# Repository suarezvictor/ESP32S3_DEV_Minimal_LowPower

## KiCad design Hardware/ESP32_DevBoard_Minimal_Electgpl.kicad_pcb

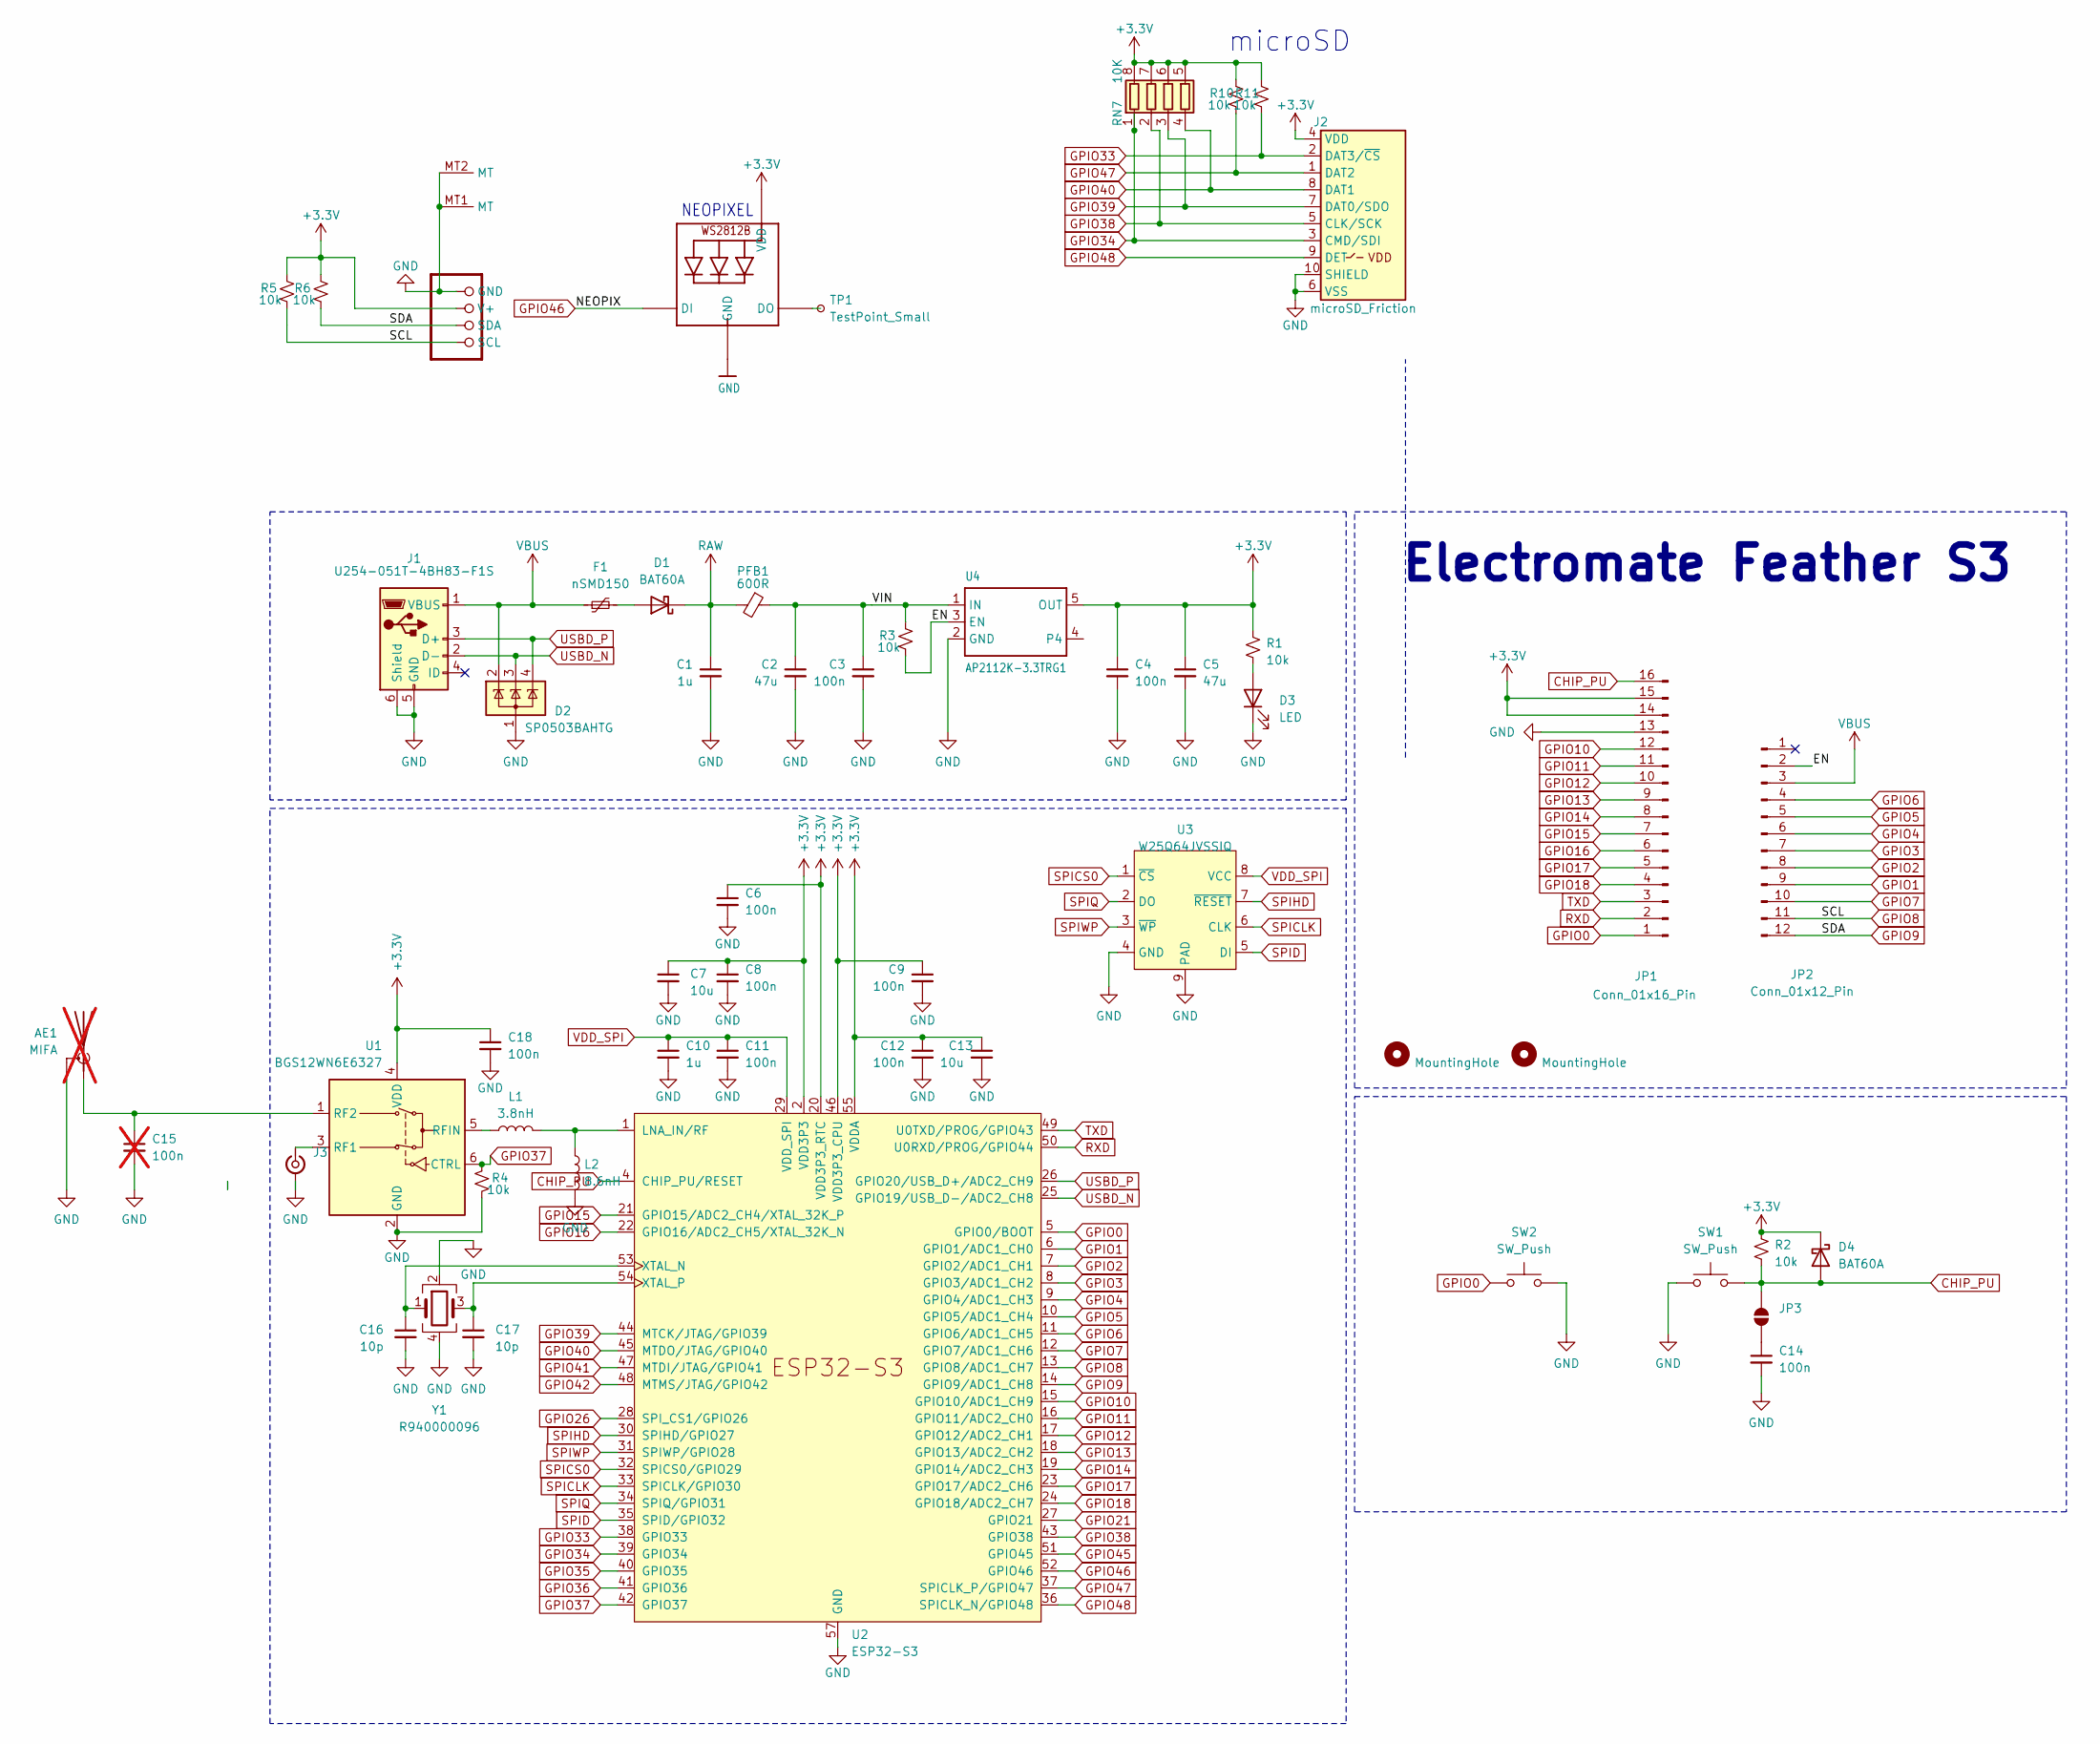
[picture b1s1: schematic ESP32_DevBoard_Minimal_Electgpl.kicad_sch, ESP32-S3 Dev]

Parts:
AE1: MIFA; ESPRESSIF_ESP32_MIFA_2.4GHz_Right; not fitted
C1: 1u; C_0402_1005Metric; MPN CL05X105KP5NNNC; LCSC Part Number C5673
C2: 47u; C_0603_1608Metric; MPN GRM188R60J476ME15D; LCSC Part Number C124129
C3: 100n; C_0402_1005Metric; MPN CC0402KRX7R9BB104; LCSC Part Number C1591
C4, C6, C8, C9, C11, C12, C14, C18: 100n; C_0402_1005Metric; MPN CC0402KRX7R9BB104; LCSC RE0187778
C5: 47u; C_0603_1608Metric; MPN GRM188R60J476ME15D; LCSC CA0135493
C7, C13: 10u; C_0603_1608Metric; MPN GCM188D70J106ME36D; LCSC CA0384128
C10: 1u; C_0402_1005Metric; MPN CL05X105KP5NNNC; LCSC CA0157860
C15: 100n; C_0402_1005Metric; not fitted
C16, C17: 10p; C_0402_1005Metric; MPN GRM1555C1H100GA01D; LCSC CA0137027
CONN1: QUICC; JST_SH_BM04B-SRSS-TB_1x04-1MP_P1.00mm_Vertical; MPN BM04B-SRSS-TB(LF)(SN); LCSC Part Number C160390
D1, D4: BAT60A; D_SOD-323
D2: SP0503BAHTG; SOT-143; MPN SP0503BAHTG; LCSC CP0003989
D3: LED; LED_0603_1608Metric; MPN TJ-S1608B06HQYJY-A3; LCSC PH0093820
F1: nSMD150; Fuse_1206_3216Metric_Pad1.42x1.75mm_HandSolder; MPN nSMD075-16V; LCSC CP0107097
H1, H2: MountingHole
J1: U254-051T-4BH83-F1S; USB_Micro-B_XKB_U254-051T-4BH83-F1S; MPN U254-051T-4BH83-F1S; LCSC CO0893195
J2: microSD_Friction; TF-SMD_TF-018
J3: Conn_Coaxial_Small; U.FL_Molex_MCRF_73412-0110_Vertical; MPN 734120114; LCSC Part Number C277719
JP1: Conn_01x16_Pin; PinHeader_1x16_P2.54mm_Vertical
JP2: Conn_01x12_Pin; PinHeader_1x12_P2.54mm_Vertical
JP3: SolderJumper_2_Open; SolderJumper-2_P1.3mm_Open_RoundedPad1.0x1.5mm
L1: 3.8nH; C_0402_1005Metric; MPN SCC1005C4N3SSP; LCSC IN0076375
L2: 8.6nH; C_0402_1005Metric; MPN SCW1005C8N2JST; LCSC IN0074484
LED1: WS2812B_SK6805_1515; LED-SMD_4P-L1.5-W1.5-BL; MPN SK6805-EC15
PFB1: 600R; C_0603_1608Metric; MPN BLM18SG331TN1D; LCSC WF0011783
R1, R2, R3, R4, R5, R6, R10, R11: 10k; R_0402_1005Metric; MPN RC0402JR-0710KL; LCSC RE0023874
RN7: 10K; R_Array_Convex_4x0402; MPN 4D02WGJ0103TCE
SW1, SW2: SW_Push; SW_Push_SPST_NO_Alps_SKRK; MPN SKRKAEE020; LCSC SW0049182
TP1: TestPoint_Small; TestPoint_Pad_D1.0mm
U1: BGS12WN6E6327; Infineon_PG-TSNP-6-10_0.7x1.1mm_0.7x1.1mm_P0.4mm; MPN BGS12WN6E6327XTSA1
U2: ESP32-S3; QFN-56-1EP_7x7mm_P0.4mm_EP5.6x5.6mm; MPN ESP32-S3FH4R2; LCSC Part Number C3013940
U3: W25Q64JVSSIQ; SOP-8_5.28x5.23mm_P1.27mm; MPN GD25Q64ESIG; LCSC IC0447018
U4: AP2112K-3.3TRG1; SOT-23-5; MPN AP2112K-3.3TRG1; LCSC Part Number C51118
Y1: R940000096; Crystal_SMD_2016-4Pin_2.0x1.6mm; MPN TAXM40M4ZHBCDT2T; LCSC Part Number C7206306

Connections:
+3.3V: C4.1, C5.1, C6.1, C7.1, C8.1, C9.1, C12.1, C13.1, C18.1, CONN1.2 (V+), D4.1 (K), J2.4 (VDD), JP1.14, JP1.15, LED1.2 (VDD), R1.1, R2.1, R5.1, R6.1, R10.1, R11.1, RN7.5 (R4.2), RN7.6 (R3.2), RN7.7 (R2.2), RN7.8 (R1.2), U1.4 (VDD), U2.2 (VDD3P3), U2.3 (VDD3P3), U2.20 (VDD3P3_RTC), U2.46 (VDD3P3_CPU), U2.55 (VDDA), U2.56 (VDDA), U4.5 (OUT); also elsewhere on the board
/EN: JP2.2, R3.2, U4.3 (EN)
/VIN: C2.1, C3.1, PFB1.1, R3.1, U4.1 (IN)
CHIP_PU: D4.2 (A), JP1.16, JP3.2 (B), R2.2, SW1.2, U2.4 (CHIP_PU/RESET)
GND: AE1.2 (Shield), C1.2, C2.2, C3.2, C4.2, C5.2, C6.2, C7.2, C8.2, C9.2, C10.2, C11.2, C12.2, C13.2, C14.2, C15.2, C16.2, C17.2, C18.2, CONN1.1 (GND), CONN1.MT1 (MT), CONN1.MT2 (MT), D2.1 (A), D3.1 (K), J1.5 (GND), J1.6 (Shield), J2.6 (VSS), J2.10 (SHIELD), J3.2 (Ext), JP1.13, L2.2, LED1.4 (GND), R4.2, SW1.1, SW2.1, U1.2 (GND), U2.57 (GND), U3.4 (GND), U3.9 (PAD), U4.2 (GND), Y1.2, Y1.4
GPIO0: JP1.1, SW2.2, U2.5 (GPIO0/BOOT)
GPIO1: JP2.9, U2.6 (GPIO1/ADC1_CH0)
GPIO2: JP2.8, U2.7 (GPIO2/ADC1_CH1)
GPIO3: JP2.7, U2.8 (GPIO3/ADC1_CH2)
GPIO4: JP2.6, U2.9 (GPIO4/ADC1_CH3)
GPIO5: JP2.5, U2.10 (GPIO5/ADC1_CH4)
GPIO6: JP2.4, U2.11 (GPIO6/ADC1_CH5)
GPIO7: JP2.10, U2.12 (GPIO7/ADC1_CH6)
GPIO8: CONN1.4 (SCL), JP2.11, R5.2, U2.13 (GPIO8/ADC1_CH7)
GPIO9: CONN1.3 (SDA), JP2.12, R6.2, U2.14 (GPIO9/ADC1_CH8)
GPIO10: JP1.12, U2.15 (GPIO10/ADC1_CH9)
GPIO11: JP1.11, U2.16 (GPIO11/ADC2_CH0)
GPIO12: JP1.10, U2.17 (GPIO12/ADC2_CH1)
GPIO13: JP1.9, U2.18 (GPIO13/ADC2_CH2)
GPIO14: JP1.8, U2.19 (GPIO14/ADC2_CH3)
GPIO15: JP1.7, U2.21 (GPIO15/ADC2_CH4/XTAL_32K_P)
GPIO16: JP1.6, U2.22 (GPIO16/ADC2_CH5/XTAL_32K_N)
GPIO17: JP1.5, U2.23 (GPIO17/ADC2_CH6)
GPIO18: JP1.4, U2.24 (GPIO18/ADC2_CH7)
GPIO21: U2.27 (GPIO21)
GPIO26: U2.28 (SPI_CS1/GPIO26)
GPIO33: J2.2 (DAT3/~CS), R11.2, U2.38 (GPIO33)
GPIO34: J2.3 (CMD/SDI), RN7.1 (R1.1), U2.39 (GPIO34); also elsewhere on the board
GPIO35: U2.40 (GPIO35)
GPIO36: U2.41 (GPIO36)
GPIO37: R4.1, U1.6 (CTRL), U2.42 (GPIO37)
GPIO38: J2.5 (CLK/SCK), RN7.2 (R2.1), U2.43 (GPIO38); also elsewhere on the board
GPIO39: J2.7 (DAT0/SDO), RN7.3 (R3.1), U2.44 (MTCK/JTAG/GPIO39); also elsewhere on the board
GPIO40: J2.8 (DAT1), RN7.4 (R4.1), U2.45 (MTDO/JTAG/GPIO40); also elsewhere on the board
GPIO41: U2.47 (MTDI/JTAG/GPIO41)
GPIO42: U2.48 (MTMS/JTAG/GPIO42)
GPIO45: U2.51 (GPIO45)
GPIO46: LED1.1 (DI), U2.52 (GPIO46)
GPIO47: J2.1 (DAT2), R10.2, U2.37 (SPICLK_P/GPIO47)
GPIO48: J2.9 (DET), U2.36 (SPICLK_N/GPIO48)
unnamed: AE1.1 (A), C15.1, U1.1 (RF2)
unnamed: D1.2 (A), F1.2
unnamed: D3.2 (A), R1.2
unnamed: J3.1 (In), U1.3 (RF1)
unnamed: C14.1, JP3.1 (A)
unnamed: LED1.3 (DO), TP1.1
unnamed: L1.1, U1.5 (RFIN)
unnamed: L1.2, L2.1, U2.1 (LNA_IN/RF)
unnamed: C16.1, U2.53 (XTAL_N), Y1.1
unnamed: C17.1, U2.54 (XTAL_P), Y1.3
RAW: C1.1, D1.1 (K), PFB1.2
RXD: JP1.2, U2.50 (U0RXD/PROG/GPIO44)
SPICLK: U2.33 (SPICLK/GPIO30), U3.6 (CLK)
SPICS0: U2.32 (SPICS0/GPIO29), U3.1 (~CS)
SPID: U2.35 (SPID/GPIO32), U3.5 (DI)
SPIHD: U2.30 (SPIHD/GPIO27), U3.7 (~RESET)
SPIQ: U2.34 (SPIQ/GPIO31), U3.2 (DO)
SPIWP: U2.31 (SPIWP/GPIO28), U3.3 (~WP)
TXD: JP1.3, U2.49 (U0TXD/PROG/GPIO43)
USBD_N: D2.3 (K), J1.2 (D-), U2.25 (GPIO19/USB_D-/ADC2_CH8)
USBD_P: D2.4 (K), J1.3 (D+), U2.26 (GPIO20/USB_D+/ADC2_CH9)
VBUS: D2.2 (K), F1.1, J1.1 (VBUS), JP2.3
VDD_SPI: C10.1, C11.1, U2.29 (VDD_SPI), U3.8 (VCC)

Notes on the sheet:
Electromate Feather S3
NEOPIXEL
microSD

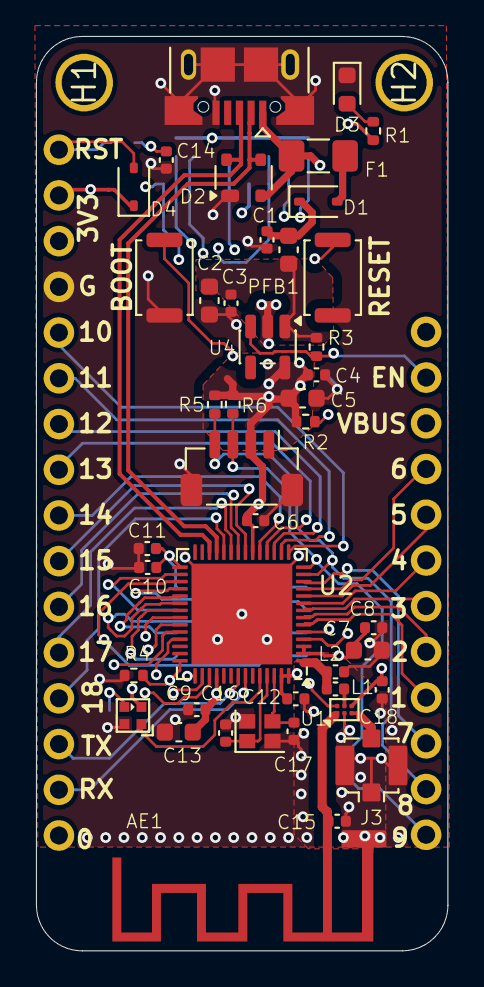
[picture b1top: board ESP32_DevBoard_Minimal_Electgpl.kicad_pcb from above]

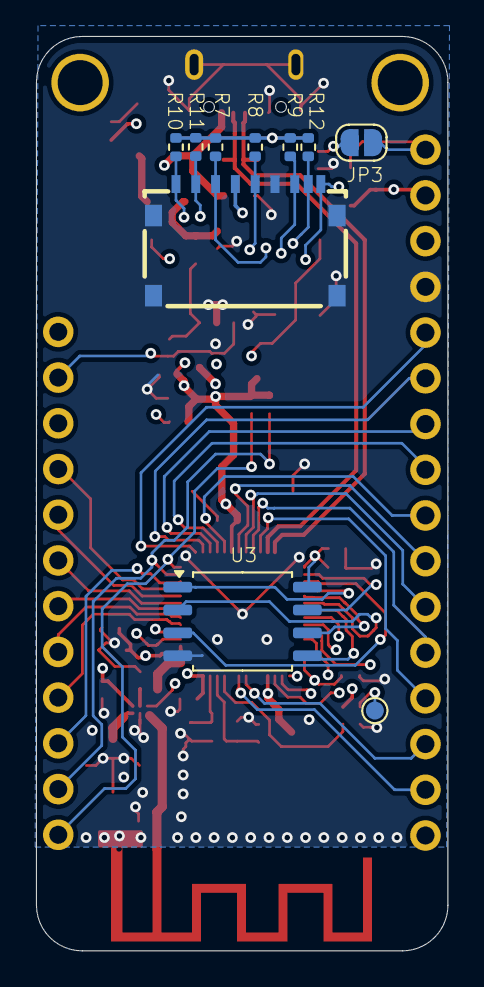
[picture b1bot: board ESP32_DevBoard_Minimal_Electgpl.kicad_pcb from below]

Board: 4 copper layers, 22.9 x 50.8 mm, 57 parts (12 on the bottom side), 56 nets.

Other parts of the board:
R7, R8, R9, R12: 10k; R_0402_1005Metric

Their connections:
+3.3V: R7.1, R8.1, R9.1, R12.1; also elsewhere on the board
GPIO34: R7.2; also elsewhere on the board
GPIO38: R8.2; also elsewhere on the board
GPIO39: R9.2; also elsewhere on the board
GPIO40: R12.2; also elsewhere on the board

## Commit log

2025-11-26 feather format and DRC check
2025-12-01 add u.FL antenna connector

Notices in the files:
Hardware/ESP32_DevBoard_Minimal_Electgpl.kicad_sch:
Based on elecgpl, MIT license
and Adafruit Feather ESP32-S3 PCB, CC BY-SA 3.0 license
